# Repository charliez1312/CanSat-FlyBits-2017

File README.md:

# CanSat-FlyBits-2017
Cansat competition / FlyBits 2017 http://flybits.8u.cz/

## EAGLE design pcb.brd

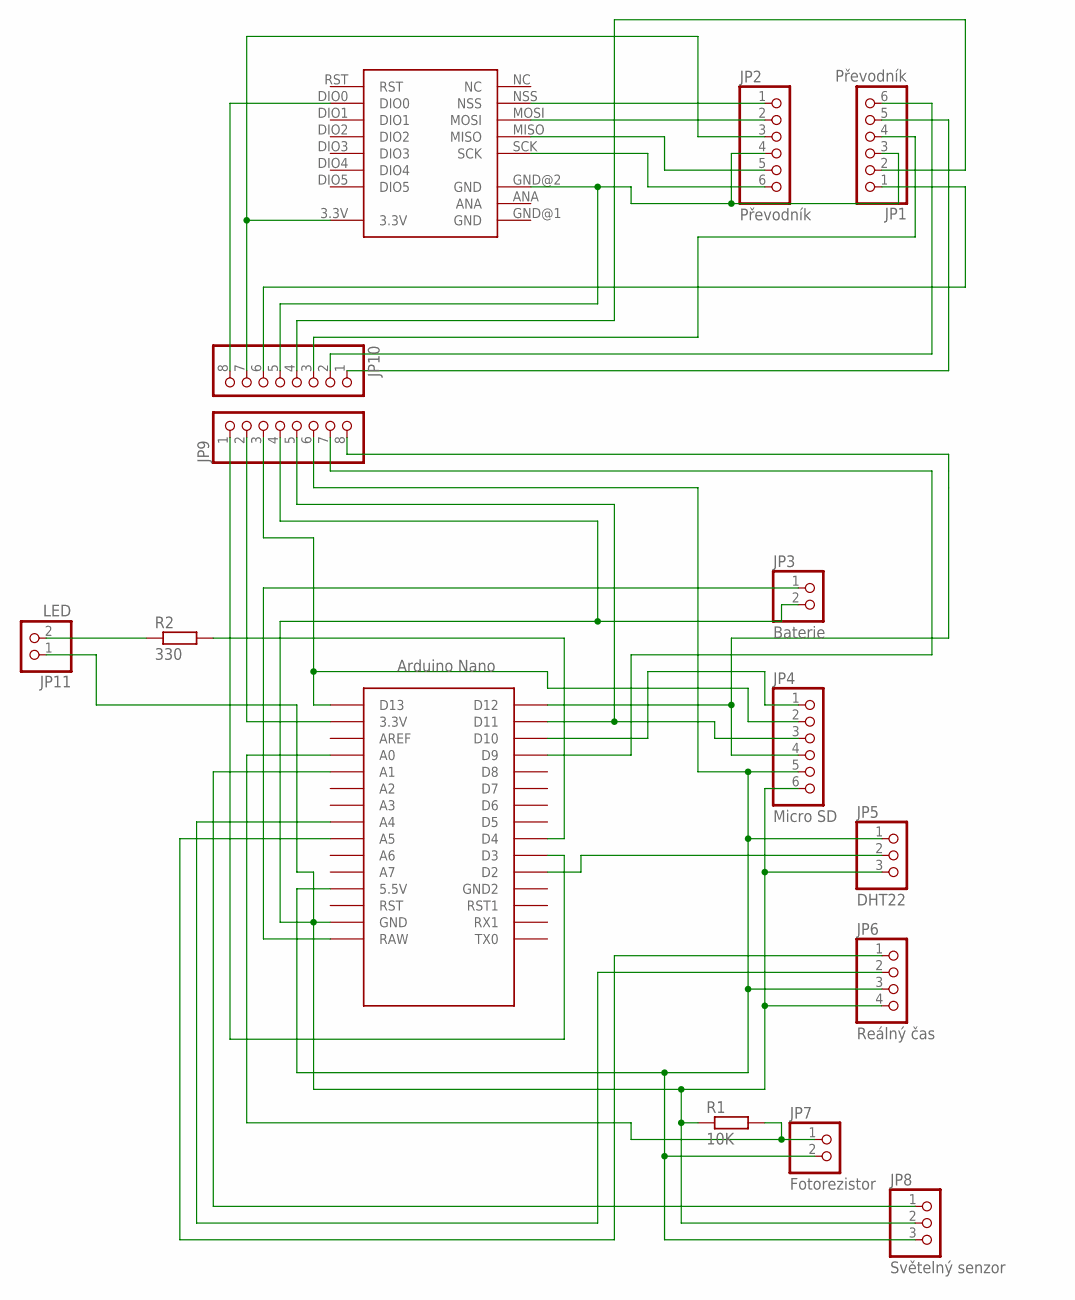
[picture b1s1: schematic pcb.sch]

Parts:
JP1, JP2: Převodník; 1X06
JP3: Baterie; 1X02
JP4: Micro SD; 1X06
JP5: DHT22; 1X03
JP6: Reálný čas; 1X04
JP7: Fotorezistor; 1X02
JP8: Světelný senzor; 1X03
JP9, JP10: PINHD-1X8; 1X08
JP11: LED; 1X02
R1: 10K; 0204/7
R2: 330; 0204/7
RFM69: RFM69; 20X16BOARD
U$1: NANO

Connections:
GND: RFM69.GND@1 (GND)
unnamed: JP4.5, JP5.1, JP6.3, JP7.2, JP8.3, JP9.6, U$1.5V (5.5V)
unnamed: JP3.2, JP4.6, JP5.3, JP6.4, JP8.2, JP9.4, JP11.1, R1.1, U$1.GND
unnamed: JP4.4, JP9.8, U$1.D12
unnamed: JP1.2, JP10.4
unnamed: JP1.1, JP10.6
unnamed: JP4.1, U$1.D10
unnamed: JP3.1, U$1.RAW
unnamed: JP5.2, U$1.D2
unnamed: JP2.5, RFM69.MISO
unnamed: JP2.6, RFM69.SCK
unnamed: JP2.2, RFM69.MOSI
unnamed: JP2.1, RFM69.NSS
unnamed: JP2.3, JP10.7, RFM69.3.3V
unnamed: JP9.1, U$1.D3
unnamed: JP8.1, U$1.A1
unnamed: JP7.1, R1.2, U$1.A0
unnamed: JP9.7, U$1.D9
unnamed: JP6.2, U$1.A4
unnamed: JP6.1, U$1.A5
unnamed: JP10.8, RFM69.DIO0
unnamed: JP9.2, U$1.3.3V
unnamed: JP4.2, JP9.3, U$1.D13
unnamed: JP1.3, JP2.4, JP10.5, RFM69.GND@2 (GND)
unnamed: JP4.3, JP9.5, U$1.D11
unnamed: JP1.4, JP10.3
unnamed: JP1.6, JP10.2
unnamed: JP1.5, JP10.1
unnamed: JP11.2, R2.1
unnamed: R2.2, U$1.D4
NC: RFM69.NC

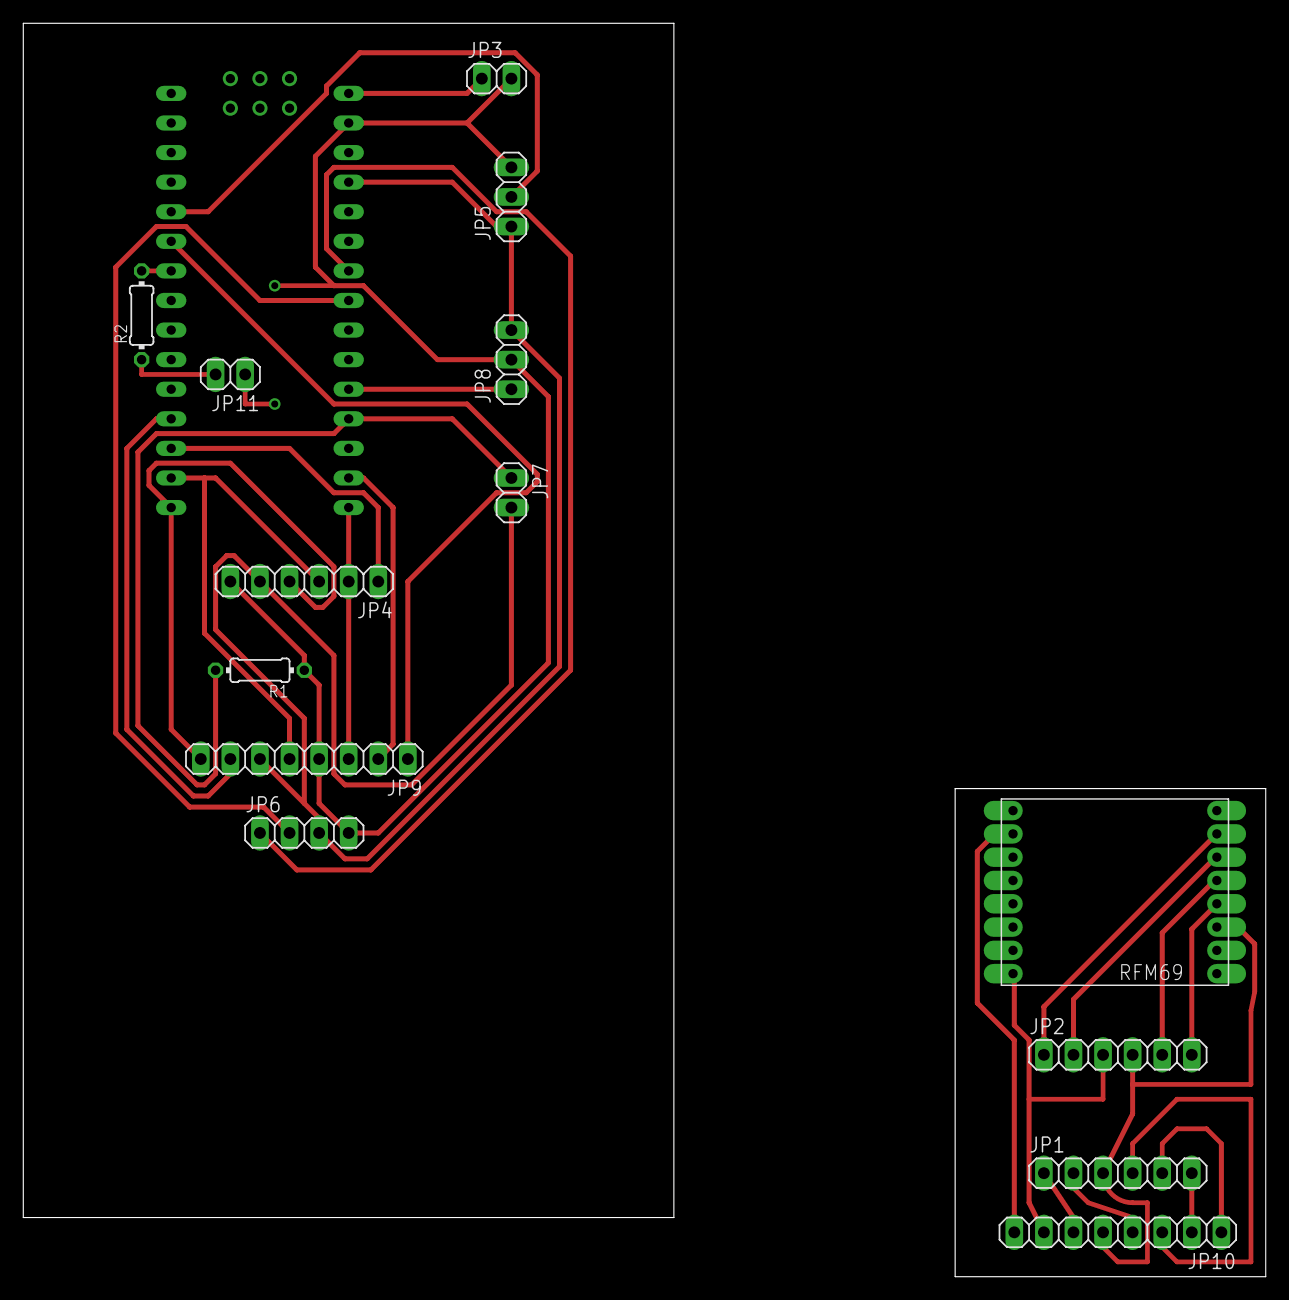
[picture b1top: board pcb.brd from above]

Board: 2 copper layers, 106.7 x 107.6 mm, 15 parts (0 on the bottom side), 29 nets.

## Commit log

2017-03-15 Rename Values.scad to Arduino_case_values.scad
